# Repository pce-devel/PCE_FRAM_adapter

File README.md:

# FRAM converter boards

The PC Engine series of systems has a different game-save storage system than most people
these days have gotten used to.  It used a 2KB static RAM.  This wasn't in the cartridges
themselves; initially, it was sold as pat of an add-on to the system: The Tennokoe 2,
"Voice from Heaven".  In later systems like the Duo series, it would be integrated into
the system unit, yet still be limited to 2KB static RAM.

You're probably thinking, "Static RAM is volatile - it loses its contents when the power
is shut off", and you'd be right.  There really weren't any non-volatiole options at the
time.  Instead, they used batteries or large capacitors to apply continuous power to the
memory, so that it would not lose its contents.  In the case of the Tennokoe 2, 2 "AA"
cells were used; in the case of the Duo, a large capacitor was used.

I have lost a few game saves on my Duo because I failed to turn the system on for a period
of time long enough to lose its contents... probably about 1 to 2 weeks.

Because of this, I was inspired to replace the SRAM with modern FeRAM to make it
non-volatile.  But the Duo is a tighter-packed PC board with surface-mount chips, so I felt it
was easier to first test the idea on the Tennokoe 2, which uses a DIP SRAM chip.

I have followed up with a design for a flex PCB to use with surface-mount chips in order to
be suitable for my Duo, and it also works well.

I chose to use the Cypress FM16W08 chip, which can handle 5V, has timing which is
equal to or better than the SRAM it is replacing, and has a similar pinout.  But I still
needed to make adapter boards (which is what this repository is all about).

As the FeRAM is rated for 100 trillion read/write cycles, there is no
concern about lifetime under the usage in this application.

I designed the boards using the free version of EAGLE (2-layer, less than 100mm
on both X- and Y-axes).  The gerbers are included in this repository, in case you
want to get your own set made.

## Assembly/installation instructions for the FRAM-DIP board for the Tennokoe 2:

https://github.com/dshadoff/PCE_FRAM_adapter/blob/master/FRAM-DIP-assembly.md

## Assembly/installation instructions for the FRAM-SOIC board for the Duo and other machines:

https://github.com/dshadoff/PCE_FRAM_adapter/blob/master/FRAM-SOIC-assembly.md

## UPDATE: A new board for use with the PCE Shuttle Backup Memory

The Shuttle's board was designed using KiCAD. While this board is separate and distinct from
the board for the Tennokoe 2, the installation instructions are similar (sorry, but I don't
have pictures)

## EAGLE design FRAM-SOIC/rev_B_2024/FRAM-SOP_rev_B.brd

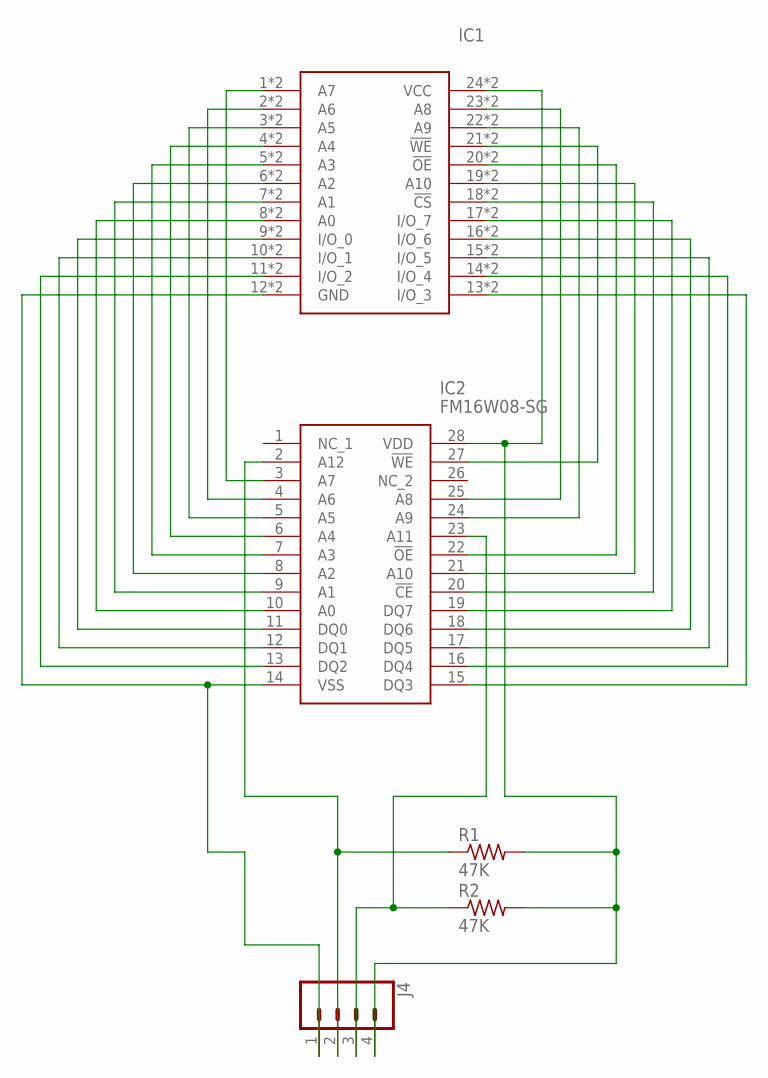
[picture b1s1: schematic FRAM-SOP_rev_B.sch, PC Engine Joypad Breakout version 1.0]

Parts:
IC1: 6116SOP-CASTELL; CASTELL_SOIC-24N
IC2: FM16W08-SG; SOIC127P1032X267-28N
J4: CONN_04SMD_RA_FEMALE; 1X04_SMD_RA_FEMALE
R1, R2: 47K; R0603

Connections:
unnamed: IC1.24 (VCC), IC1.P$24 (VCC), IC2.28 (VDD), J4.4, R1.2, R2.2
unnamed: IC1.23 (A8), IC1.P$23 (A8), IC2.25 (A8)
unnamed: IC1.22 (A9), IC1.P$22 (A9), IC2.24 (A9)
unnamed: IC1.21 (!WE), IC1.P$21 (!WE), IC2.27 (!WE)
unnamed: IC1.20 (!OE), IC1.P$20 (!OE), IC2.22 (!OE)
unnamed: IC1.19 (A10), IC1.P$19 (A10), IC2.21 (A10)
unnamed: IC1.18 (!CS), IC1.P$18 (!CS), IC2.20 (!CE)
unnamed: IC1.17 (I/O_7), IC1.P$17 (I/O_7), IC2.19 (DQ7)
unnamed: IC1.16 (I/O_6), IC1.P$16 (I/O_6), IC2.18 (DQ6)
unnamed: IC1.15 (I/O_5), IC1.P$15 (I/O_5), IC2.17 (DQ5)
unnamed: IC1.14 (I/O_4), IC1.P$14 (I/O_4), IC2.16 (DQ4)
unnamed: IC1.13 (I/O_3), IC1.P$13 (I/O_3), IC2.15 (DQ3)
unnamed: IC1.1 (A7), IC1.P$1 (A7), IC2.3 (A7)
unnamed: IC1.2 (A6), IC1.P$2 (A6), IC2.4 (A6)
unnamed: IC1.3 (A5), IC1.P$3 (A5), IC2.5 (A5)
unnamed: IC1.4 (A4), IC1.P$4 (A4), IC2.6 (A4)
unnamed: IC1.5 (A3), IC1.P$5 (A3), IC2.7 (A3)
unnamed: IC1.6 (A2), IC1.P$6 (A2), IC2.8 (A2)
unnamed: IC1.7 (A1), IC1.P$7 (A1), IC2.9 (A1)
unnamed: IC1.8 (A0), IC1.P$8 (A0), IC2.10 (A0)
unnamed: IC1.9 (I/O_0), IC1.P$9 (I/O_0), IC2.11 (DQ0)
unnamed: IC1.10 (I/O_1), IC1.P$10 (I/O_1), IC2.12 (DQ1)
unnamed: IC1.11 (I/O_2), IC1.P$11 (I/O_2), IC2.13 (DQ2)
unnamed: IC2.2 (A12), J4.2, R1.1
unnamed: IC1.12 (GND), IC1.P$12 (GND), IC2.14 (VSS), J4.1
unnamed: IC2.23 (A11), J4.3, R2.1

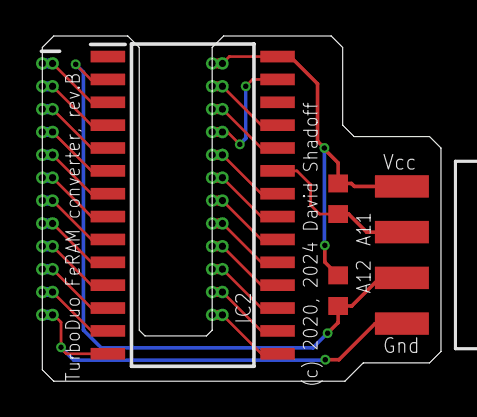
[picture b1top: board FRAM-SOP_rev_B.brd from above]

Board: 2 copper layers, 22.1 x 19.2 mm, 5 parts (0 on the bottom side), 26 nets.

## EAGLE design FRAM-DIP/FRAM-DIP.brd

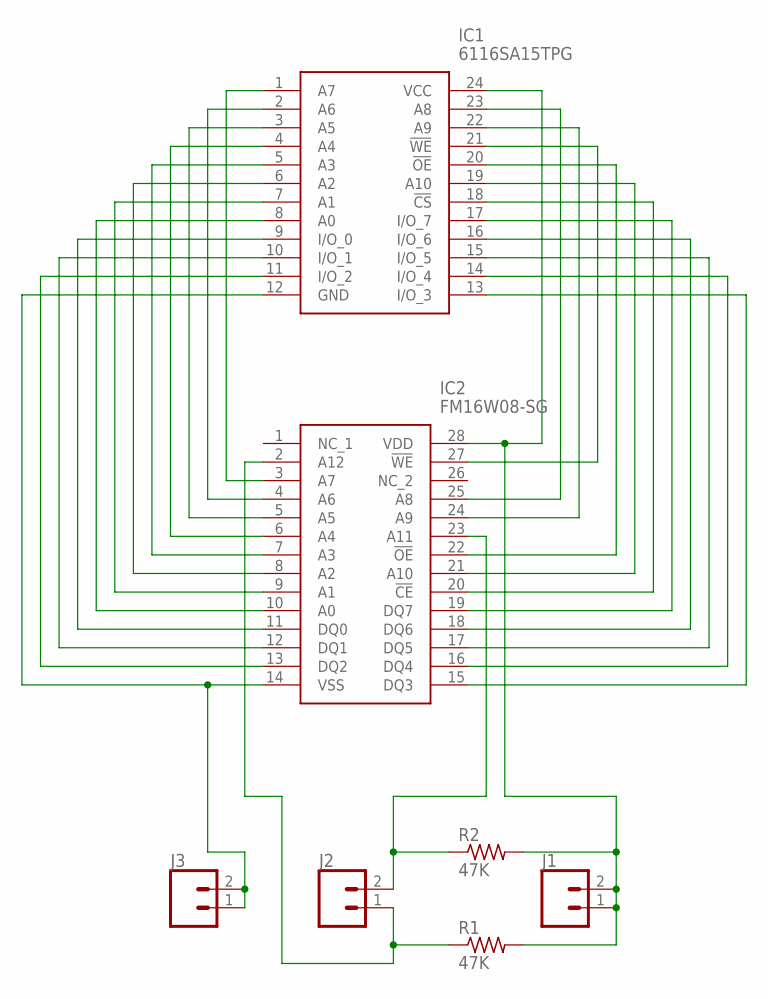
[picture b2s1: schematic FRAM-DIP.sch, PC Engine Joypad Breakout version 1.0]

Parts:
IC1: 6116SA15TPG; DIP864W51P254L3169H381Q24N
IC2: FM16W08-SG; SOIC127P1032X267-28N
J1, J2, J3: CONN_02; 1X02
R1, R2: 47K; R0805

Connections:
unnamed: IC1.24 (VCC), IC2.28 (VDD), J1.1, J1.2, R1.2, R2.2
unnamed: IC1.23 (A8), IC2.25 (A8)
unnamed: IC1.22 (A9), IC2.24 (A9)
unnamed: IC1.21 (!WE), IC2.27 (!WE)
unnamed: IC1.20 (!OE), IC2.22 (!OE)
unnamed: IC1.19 (A10), IC2.21 (A10)
unnamed: IC1.18 (!CS), IC2.20 (!CE)
unnamed: IC1.17 (I/O_7), IC2.19 (DQ7)
unnamed: IC1.16 (I/O_6), IC2.18 (DQ6)
unnamed: IC1.15 (I/O_5), IC2.17 (DQ5)
unnamed: IC1.14 (I/O_4), IC2.16 (DQ4)
unnamed: IC1.13 (I/O_3), IC2.15 (DQ3)
unnamed: IC1.1 (A7), IC2.3 (A7)
unnamed: IC1.2 (A6), IC2.4 (A6)
unnamed: IC1.3 (A5), IC2.5 (A5)
unnamed: IC1.4 (A4), IC2.6 (A4)
unnamed: IC1.5 (A3), IC2.7 (A3)
unnamed: IC1.6 (A2), IC2.8 (A2)
unnamed: IC1.7 (A1), IC2.9 (A1)
unnamed: IC1.8 (A0), IC2.10 (A0)
unnamed: IC1.9 (I/O_0), IC2.11 (DQ0)
unnamed: IC1.10 (I/O_1), IC2.12 (DQ1)
unnamed: IC1.11 (I/O_2), IC2.13 (DQ2)
unnamed: IC2.2 (A12), J2.1, R1.1
unnamed: IC2.23 (A11), J2.2, R2.1
unnamed: IC1.12 (GND), IC2.14 (VSS), J3.1, J3.2

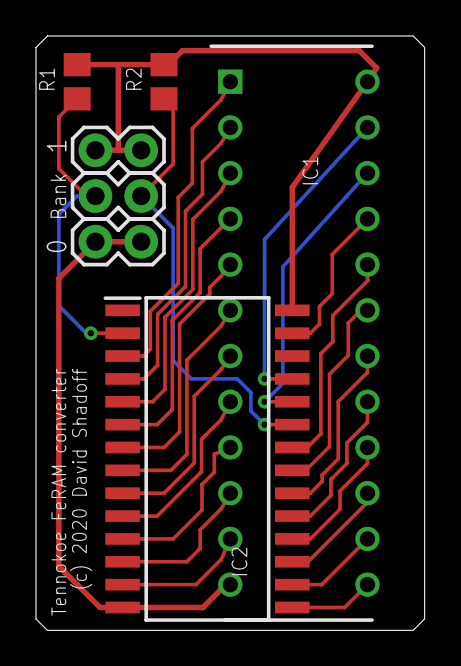
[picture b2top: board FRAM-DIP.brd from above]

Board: 2 copper layers, 21.6 x 33.0 mm, 7 parts (0 on the bottom side), 26 nets.

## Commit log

2020-07-02 Initial commit
    Initial commit; board to replace DIP SRAM in Tennokoe 2 unit
2020-07-02 Fix typo
2020-07-08 Update Installation documents
2020-07-08 Edits
2020-07-08 More edits
2020-07-11 Add surface-mount version
    A surface-mount version, to support the Duo machine, is added
2020-07-11 Add SOIC board
2024-04-01 Create a new revision of the FRAM SOP board
2026-01-11 Add FRAM adapter for PCE Shuttle Backup Memory Unti

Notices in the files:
FRAM-DIP/FRAM-DIP.brd:
(c) 2020 David Shadoff
FRAM-SOIC/rev_B_2024/FRAM-SOP_rev_B.brd:
(c) 2020, 2024 David Shadoff
parts and their libraries:
SparkFun-Connectors: Licensing: Creative Commons ShareAlike 4.0 International - https://creativecommons.org/licenses/by-sa/4.0
